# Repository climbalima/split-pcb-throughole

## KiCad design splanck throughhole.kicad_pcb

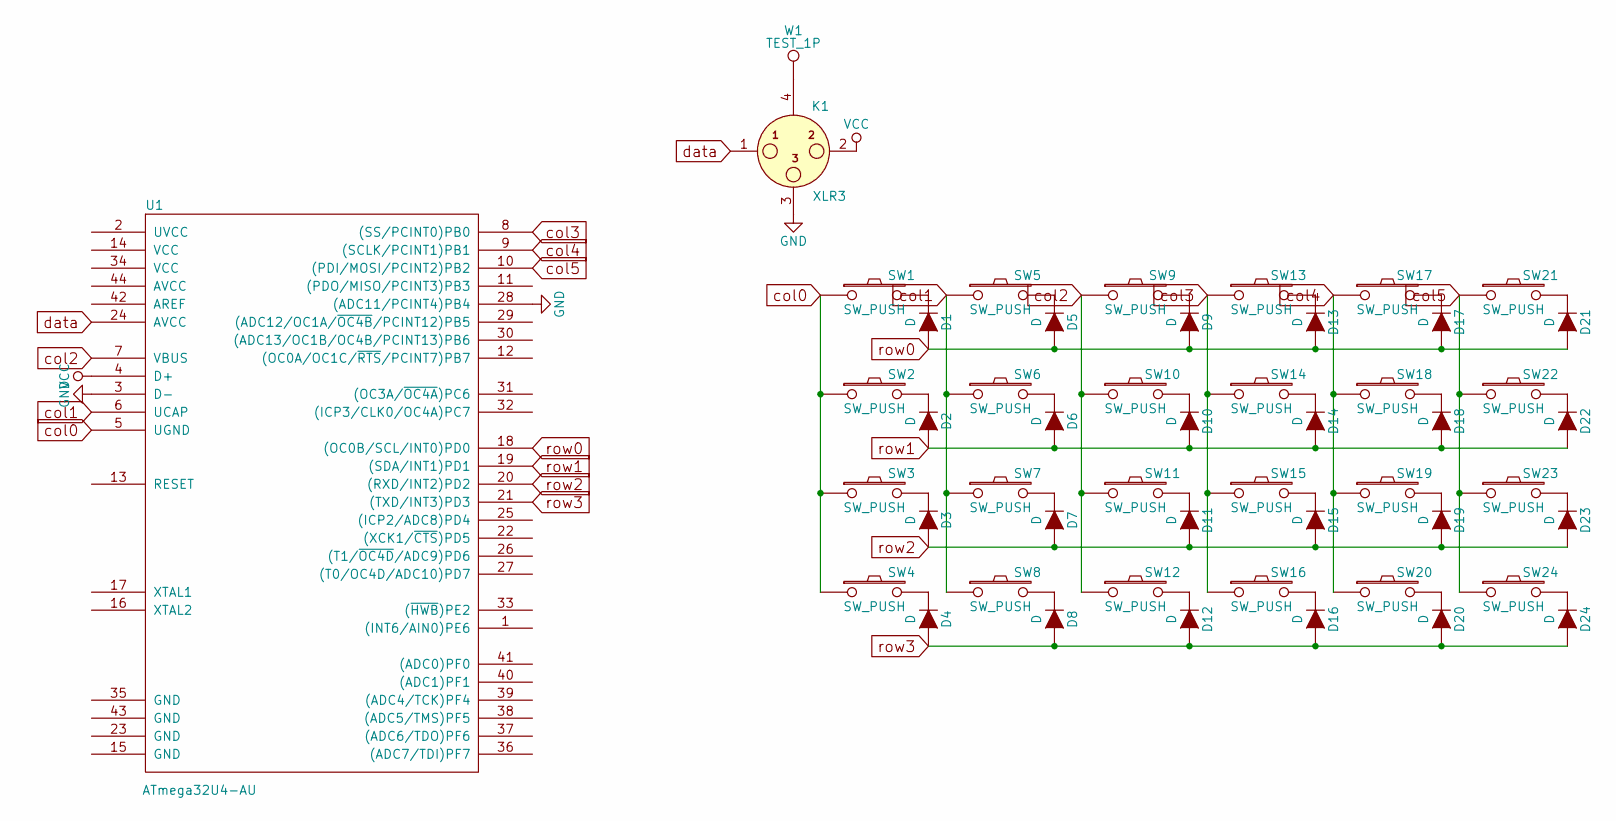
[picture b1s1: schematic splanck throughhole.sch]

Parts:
D1, D2, D3, D4, D5, D6, D7, D8, D9, D10, D11, D12, D13, D14, D15, D16, D17, D18, D19, D20, D21, D22, D23, D24: D; DIODE
K1: XLR3; 4pin35mmAudio
SW1, SW2, SW3, SW4, SW5, SW6, SW7, SW8, SW9, SW10, SW11, SW12, SW13, SW14, SW15, SW16, SW17, SW18, SW19, SW20, SW21, SW22, SW23, SW24: SW_PUSH; CHERRY_PCB_100H
U1: ATmega32U4-AU; TEENSY_2.0
W1: TEST_1P; SolderWirePad_single_0-8mmDrill

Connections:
GND: K1.3, U1.3 (D-), U1.28 ((ADC11/PCINT4)PB4)
unnamed: D1.1 (K), SW1.2
unnamed: D2.1 (K), SW2.2
unnamed: D3.1 (K), SW3.2
unnamed: D4.1 (K), SW4.2
unnamed: D5.1 (K), SW5.2
unnamed: D6.1 (K), SW6.2
unnamed: D7.1 (K), SW7.2
unnamed: D8.1 (K), SW8.2
unnamed: D9.1 (K), SW9.2
unnamed: D10.1 (K), SW10.2
unnamed: D11.1 (K), SW11.2
unnamed: D12.1 (K), SW12.2
unnamed: D13.1 (K), SW13.2
unnamed: D14.1 (K), SW14.2
unnamed: D15.1 (K), SW15.2
unnamed: D16.1 (K), SW16.2
unnamed: D17.1 (K), SW17.2
unnamed: D18.1 (K), SW18.2
unnamed: D19.1 (K), SW19.2
unnamed: D20.1 (K), SW20.2
unnamed: D21.1 (K), SW21.2
unnamed: D22.1 (K), SW22.2
unnamed: D23.1 (K), SW23.2
unnamed: D24.1 (K), SW24.2
unnamed 25: K1.4, W1.1; also elsewhere on the board
VCC: K1.2, U1.4 (D+)
col0: SW1.1, SW2.1, SW3.1, SW4.1, U1.5 (UGND)
col1: SW5.1, SW6.1, SW7.1, SW8.1, U1.6 (UCAP)
col2: SW9.1, SW10.1, SW11.1, SW12.1, U1.7 (VBUS)
col3: SW13.1, SW14.1, SW15.1, SW16.1, U1.8 ((SS/PCINT0)PB0)
col4: SW17.1, SW18.1, SW19.1, SW20.1, U1.9 ((SCLK/PCINT1)PB1)
col5: SW21.1, SW22.1, SW23.1, SW24.1, U1.10 ((PDI/MOSI/PCINT2)PB2)
data: K1.1, U1.24 (AVCC)
row0: D1.2 (A), D5.2 (A), D9.2 (A), D13.2 (A), D17.2 (A), D21.2 (A), U1.18 ((OC0B/SCL/INT0)PD0)
row1: D2.2 (A), D6.2 (A), D10.2 (A), D14.2 (A), D18.2 (A), D22.2 (A), U1.19 ((SDA/INT1)PD1)
row2: D3.2 (A), D7.2 (A), D11.2 (A), D15.2 (A), D19.2 (A), D23.2 (A), U1.20 ((RXD/INT2)PD2)
row3: D4.2 (A), D8.2 (A), D12.2 (A), D16.2 (A), D20.2 (A), D24.2 (A), U1.21 ((TXD/INT3)PD3)

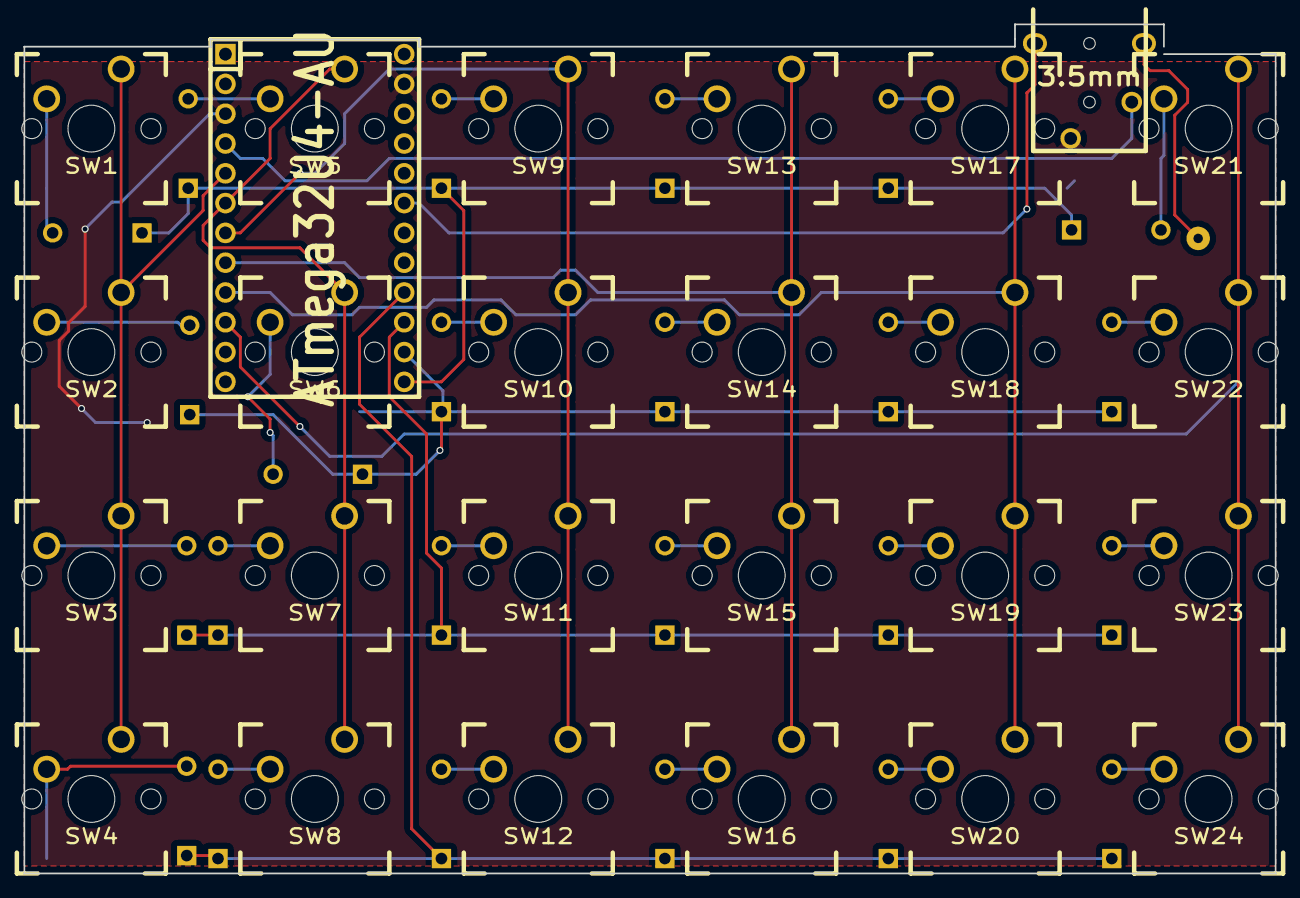
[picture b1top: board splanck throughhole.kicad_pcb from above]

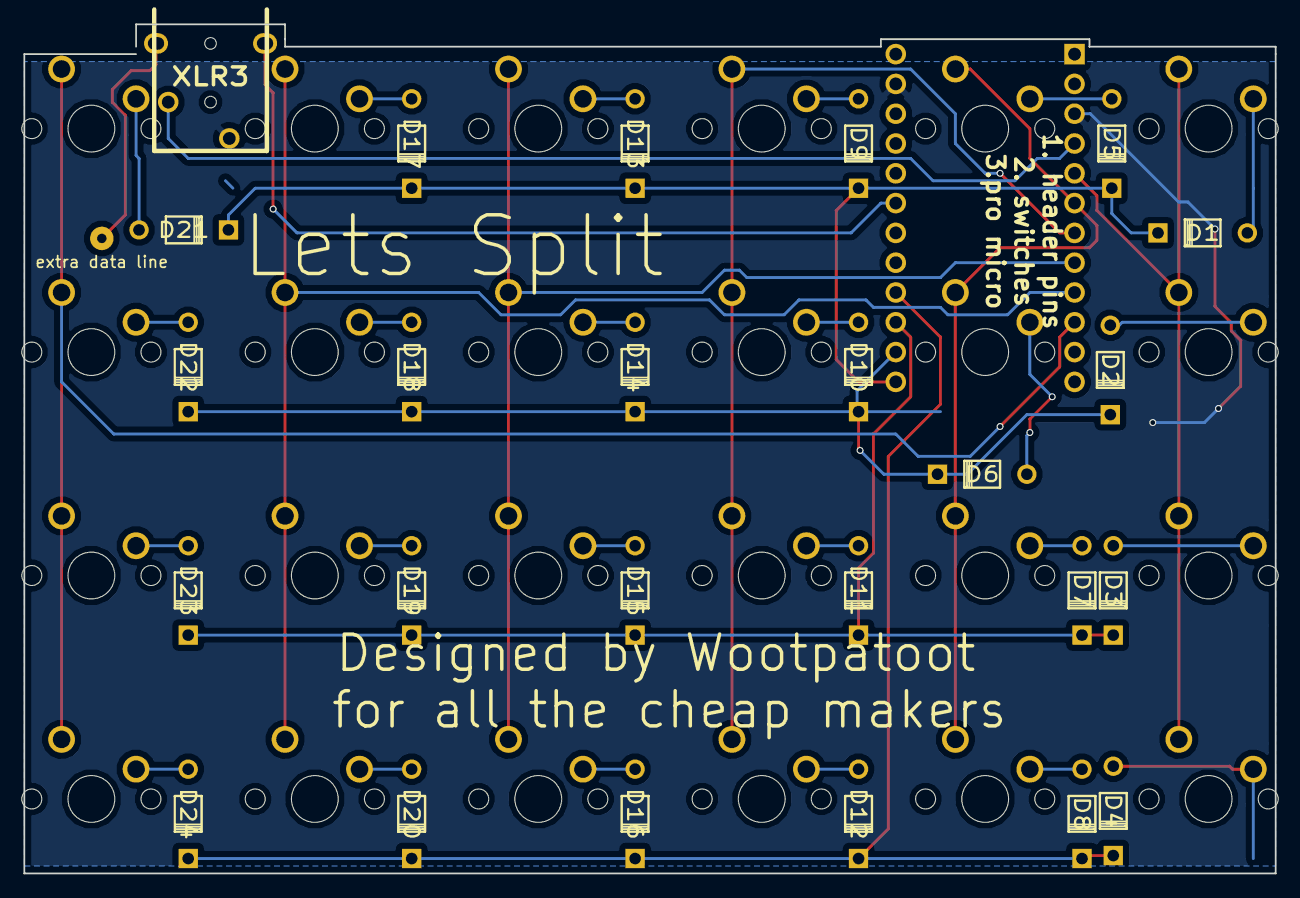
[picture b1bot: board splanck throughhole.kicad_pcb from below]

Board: 2 copper layers, 106.7 x 72.4 mm, 51 parts (25 on the bottom side), 38 nets.

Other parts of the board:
extra data line: TEST_1P; SolderWirePad_single_0-8mmDrill

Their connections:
unnamed 25: extra data line.1; also elsewhere on the board

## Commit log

2016-06-05 :space_invader: Added .gitattributes & .gitignore files
2016-06-05 added files
2016-06-19 added licence
2016-11-23 brought the pcb up to date and fixed reset pin
